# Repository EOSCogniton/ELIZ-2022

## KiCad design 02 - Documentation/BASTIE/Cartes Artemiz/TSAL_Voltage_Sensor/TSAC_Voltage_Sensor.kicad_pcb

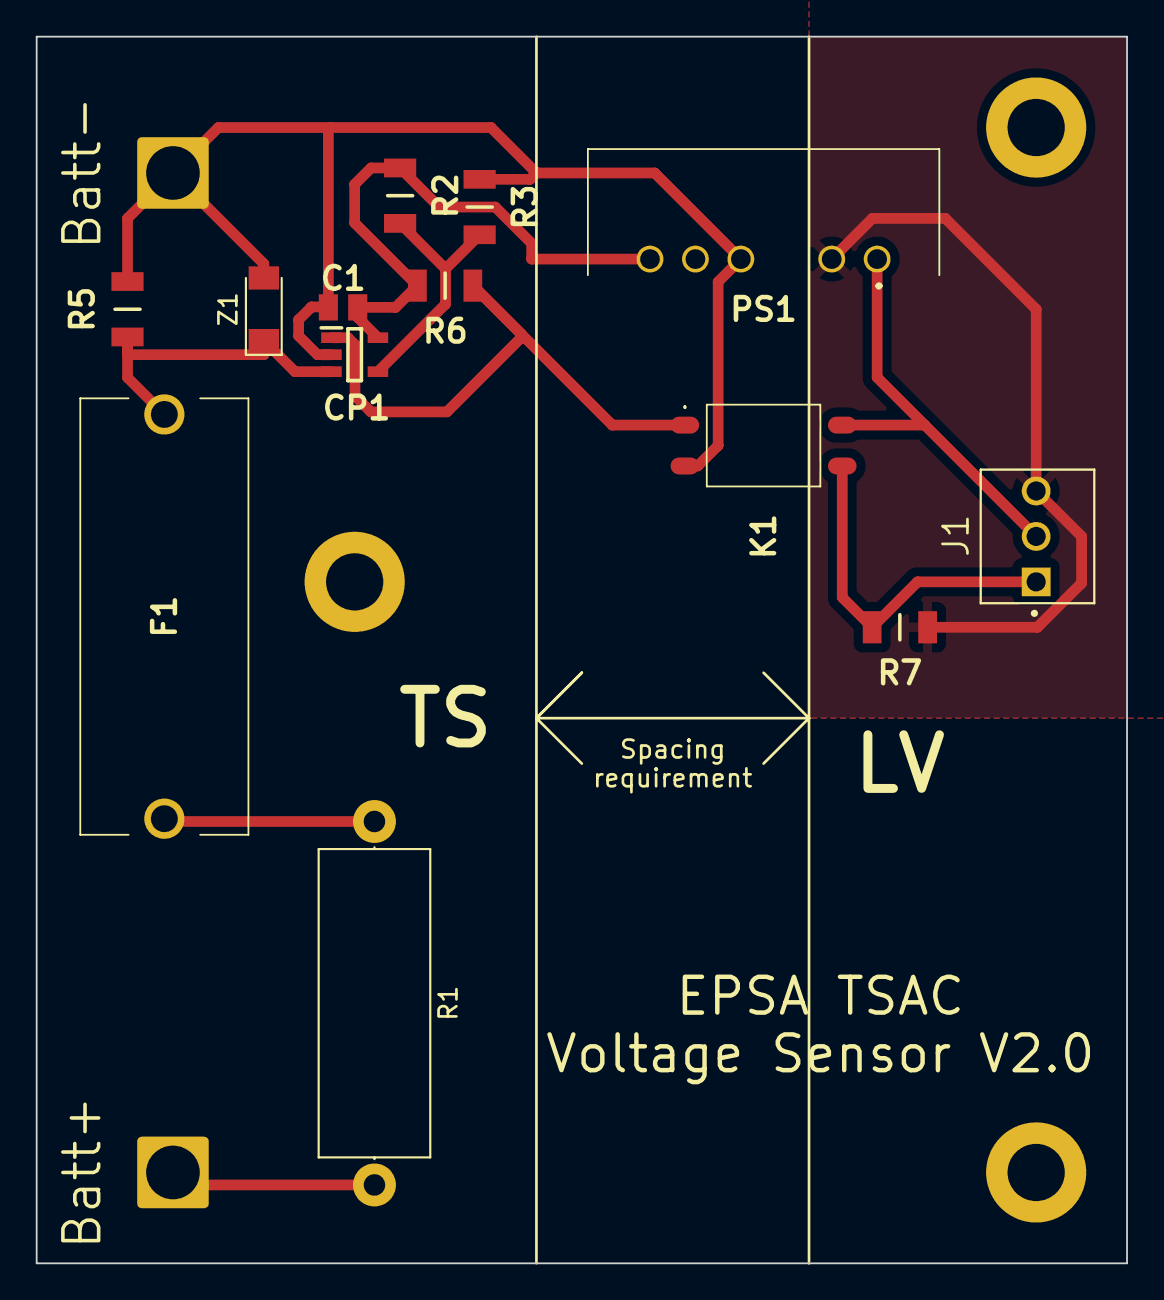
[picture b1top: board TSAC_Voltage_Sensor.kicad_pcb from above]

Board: 2 copper layers, 61.0 x 68.6 mm, 15 parts (0 on the bottom side), 10 nets.

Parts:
C1: Condensateur 0805Y1000104JXT; CAPC2012X130N
CP1: Comparateur TS391ILT; SOT95P280X145-5N
F1: Fuse; 0PTF0078P
J1: 3P Droit 22-11-2032; MOLEX_22-11-2032
K1: SSR CPC1394GR; CPC1394GR
PS1: Alim Iso PDM2-S5-S5-S; PDM2S5S5S
R1: Résistance RK73H2BLTDD2152F; R_Axial_DIN0617_L17.0mm_D6.0mm_P20.32mm_Horizontal
R2, R3, R5, R6, R7: Résistance RK73H2BLTDD2152F; RESC3216X70N
TP1, TP2: TestPoint; SolderWire-2.5sqmm_1x01_D2.4mm_OD3.6mm
Z1: Zener TZM5224B-GS08; D_MiniMELF

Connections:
0: C1.1, CP1.2 (VCC-), K1.2 (-_CONTROL), PS1.4 (0V), R3.2, R5.1, TP2.1, Z1.2
+5V: C1.2, CP1.5 (VCC+), PS1.6 (+VO), R2.2, R6.2
+5VA: J1.2, K1.4 (LOAD_2), PS1.1 (VIN)
+BATT: R1.2, TP1.1
Comp: CP1.1 (OUT), K1.1 (+_CONTROL), R6.1
Exit: J1.1, K1.3 (LOAD_1), R7.2
GND: J1.3, PS1.2 (GND), R7.1
unnamed: CP1.3 (IN-), F1.2, R5.2, Z1.1
unnamed: CP1.4 (IN+), R2.1, R3.1
unnamed: F1.1, R1.1

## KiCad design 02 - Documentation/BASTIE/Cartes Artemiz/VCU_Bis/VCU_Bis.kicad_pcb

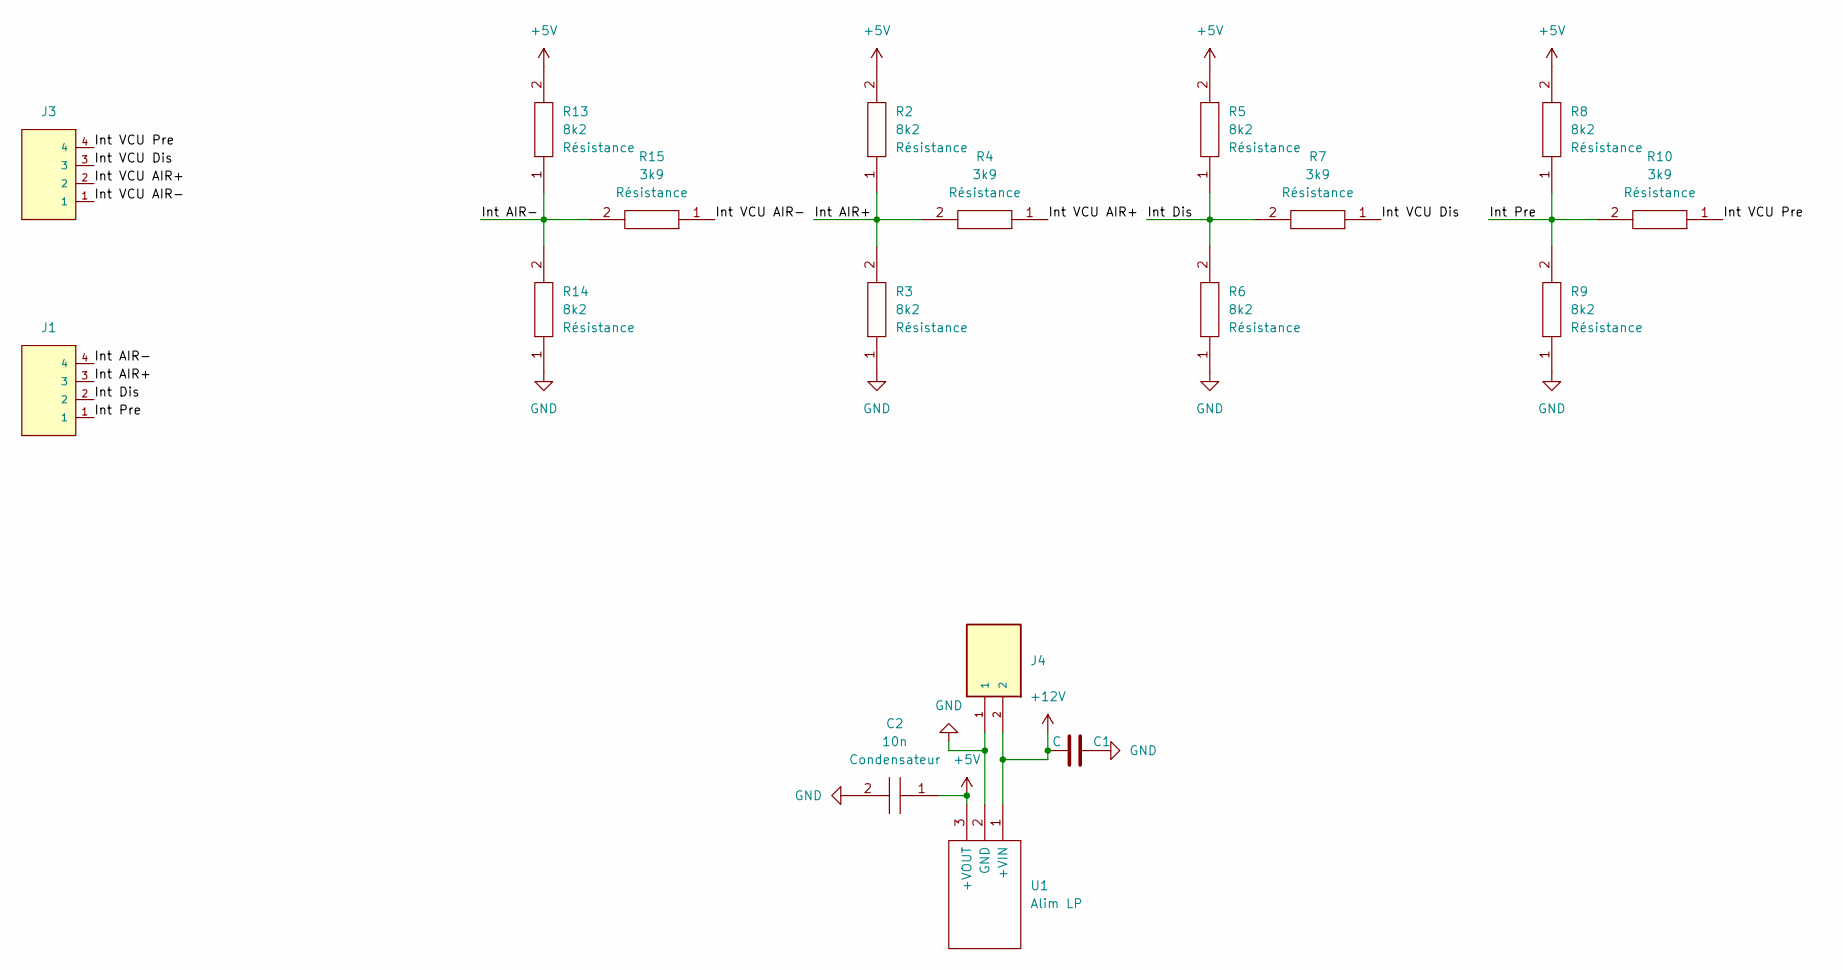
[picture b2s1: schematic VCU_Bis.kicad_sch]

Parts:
C1: C; CP_Radial_D5.0mm_P2.00mm
C2: 10n; CAPC2012X130N; Manufacturer_Part_Number 0805Y1000104JXT
J1, J3: 4P Droit 22-11-2042; MOLEX_22-11-2042; Manufacturer_Part_Number 22-11-2042; Mouser Part Number 538-22-11-2042
J4: 2P Droit 2-11-2022; MOLEX_22-11-2022; Manufacturer_Part_Number 22-11-2022; Mouser Part Number 538-22-11-2022
R2, R3, R5, R6, R8, R9, R13, R14: 8k2; RESC3216X70N; Manufacturer_Part_Number RK73H2BLTDD2152F; Mouser Part Number N/A
R4, R7, R10, R15: 3k9; RESC3216X70N; Manufacturer_Part_Number RK73H2BLTDD2152F; Mouser Part Number N/A
U1: Alim LP TSR_0.5-2450; TSR-0.5-2433; Manufacturer_Part_Number TSR 0.5-2450; Mouser Part Number 495-TSR0.5-2450

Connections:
+5V: C2.1, R2.2, R5.2, R8.2, R13.2, U1.3 (+VOUT)
+12V: C1.1, J4.2, U1.1 (+VIN)
/Int AIR+: J1.3, R2.1, R3.2, R4.2
/Int AIR-: J1.4, R13.1, R14.2, R15.2
/Int Dis: J1.2, R5.1, R6.2, R7.2
/Int Pre: J1.1, R8.1, R9.2, R10.2
/Int VCU AIR+: J3.2, R4.1
/Int VCU AIR-: J3.1, R15.1
/Int VCU Dis: J3.3, R7.1
/Int VCU Pre: J3.4, R10.1
GND: C1.2, C2.2, J4.1, R3.1, R6.1, R9.1, R14.1, U1.2 (GND)

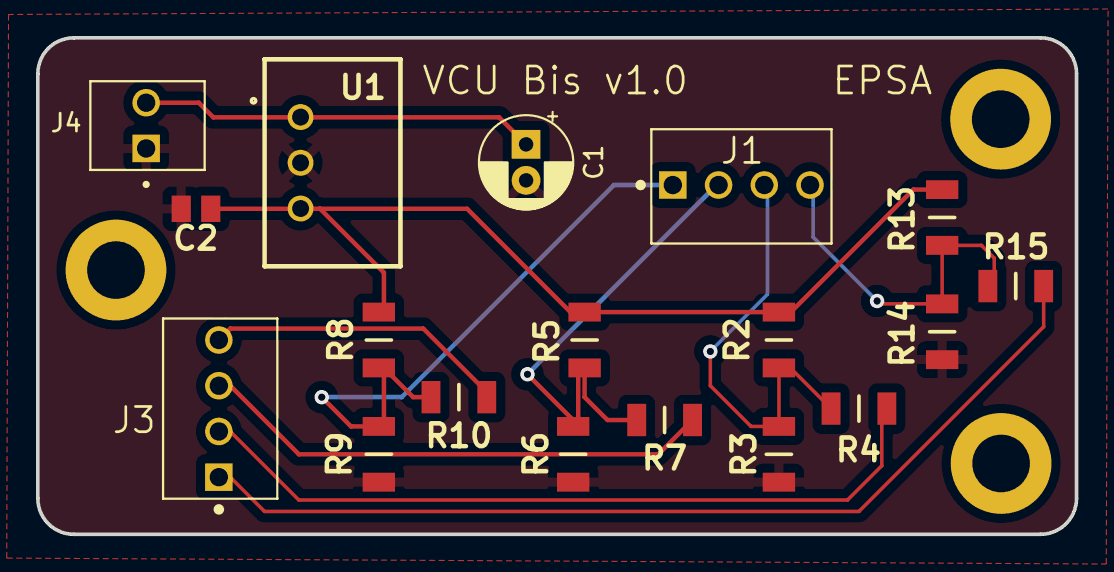
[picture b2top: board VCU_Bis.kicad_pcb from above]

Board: 2 copper layers, 57.7 x 27.6 mm, 18 parts (0 on the bottom side), 11 nets.

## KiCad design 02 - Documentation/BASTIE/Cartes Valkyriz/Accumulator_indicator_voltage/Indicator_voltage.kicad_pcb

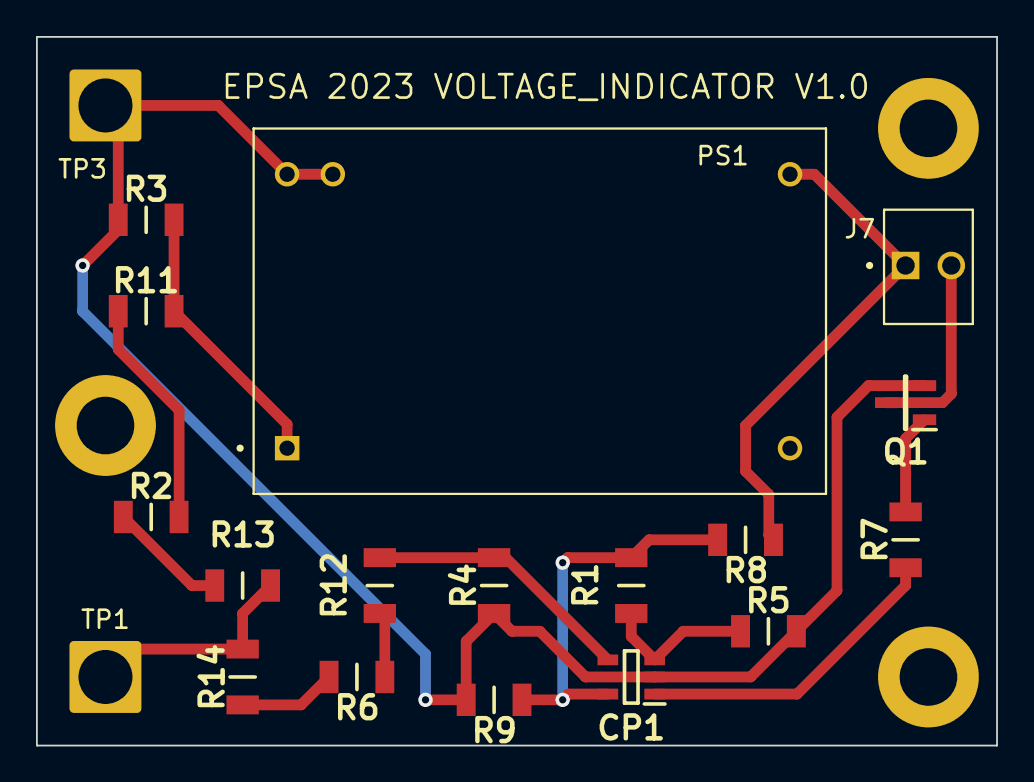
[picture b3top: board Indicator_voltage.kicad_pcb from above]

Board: 2 copper layers, 53.3 x 39.4 mm, 19 parts (0 on the bottom side), 14 nets.

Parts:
CP1: Comparateur TS391ILT; SOT95P280X145-5N
J7: 2P Droit 2-11-2022; MOLEX_22-11-2022
PS1: THR_3-7212WI; CONV_THR_3-7212WI
Q1: NMOS SQ2348ES-T1_GE3; SOT95P237X112-3N
R1: 18k; RESC3216X70N
R2, R3, R6, R11, R12, R13, R14: 390k; RESC3216X70N
R4: 10k; RESC3216X70N
R5: 2k; RESC3216X70N
R7, R9: 1k; RESC3216X70N
R8: 1k4; RESC3216X70N
TP1, TP3: type="R" model="TestPoint" lib=""; SolderWire-2.5sqmm_1x01_D2.4mm_OD3.6mm

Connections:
0: CP1.2 (VCC-), PS1.23 (-VIN(GND)), PS1.24 (-VIN(GND)), Q1.2, R3.1, R4.1, R5.2, R9.2, TP3.1
5V: CP1.5 (VCC+), R1.1, R8.2, R9.1
12V: J7.1, PS1.13 (+VOUT), R8.1
/150V: PS1.1 (+VIN(VCC)), R3.2, R11.2
HV+: R13.1, R14.2, TP1.1
LED-: J7.2, Q1.3
unnamed: CP1.4 (IN+), R4.2, R12.1
unnamed: CP1.3 (IN-), R1.2, R5.1
unnamed: CP1.1 (OUT), R7.1
unnamed: Q1.1, R7.2
unnamed: R2.2, R11.1
unnamed: R6.1, R12.2
unnamed: R2.1, R13.2
unnamed: R6.2, R14.1

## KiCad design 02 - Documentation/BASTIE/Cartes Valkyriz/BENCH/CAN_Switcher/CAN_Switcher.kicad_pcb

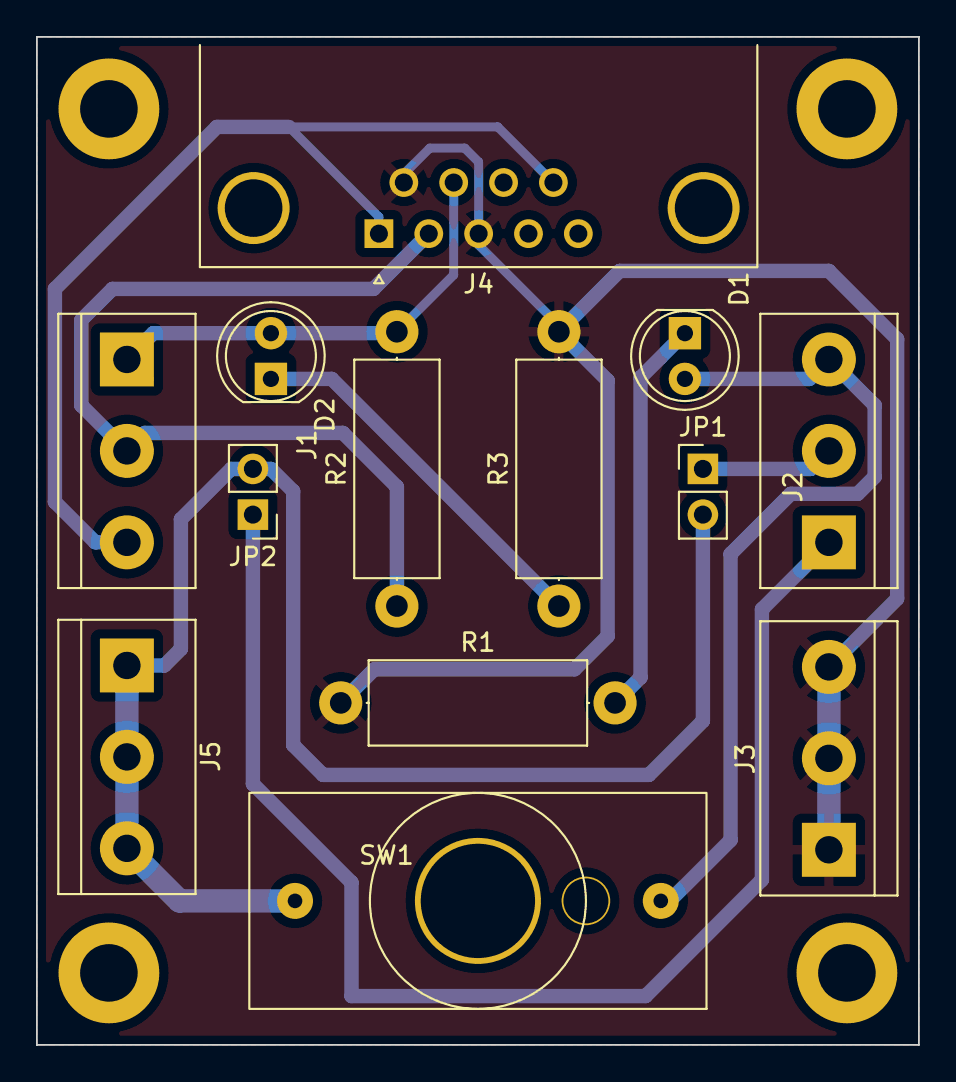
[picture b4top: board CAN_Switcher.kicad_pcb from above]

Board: 2 copper layers, 49.0 x 56.0 mm, 13 parts (0 on the bottom side), 10 nets.

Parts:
D1, D2: LED; LED_D5.0mm
J1, J2, J3, J5: Screw_Terminal_01x03; TerminalBlock_bornier-3_P5.08mm
J4: DB9_Female_MountingHoles; DSUB-9_Female_Horizontal_P2.77x2.84mm_EdgePinOffset7.70mm_H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
JP1, JP2: Jumper_2_Bridged; PinHeader_1x02_P2.54mm_Vertical
R1, R2, R3: R; R_Axial_DIN0414_L11.9mm_D4.5mm_P15.24mm_Horizontal
SW1: SW_MEC_5G; Interrupteur 1Channel

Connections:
+12V: J5.1, J5.2, J5.3, JP1.2 (B), JP2.2 (B), SW1.3 (B)
/AC Charging wake up: J2.2, JP1.1 (A)
/CAN_H_Peak: D2.2 (A), J1.1, J4.7, R2.2
/CAN_L_Peak: J1.2, J4.2, R2.1
/Can_V+: J1.3, J4.1, J4.9
/DC Charging Wake up Signal: J2.1, JP2.1 (A)
/KEYON: D1.2 (A), J2.3, SW1.2 (A)
GND: J3.1, J3.2, J3.3, J4.3, J4.6, R1.1, R3.2
unnamed: D1.1 (K), R1.2
unnamed: D2.1 (K), R3.1

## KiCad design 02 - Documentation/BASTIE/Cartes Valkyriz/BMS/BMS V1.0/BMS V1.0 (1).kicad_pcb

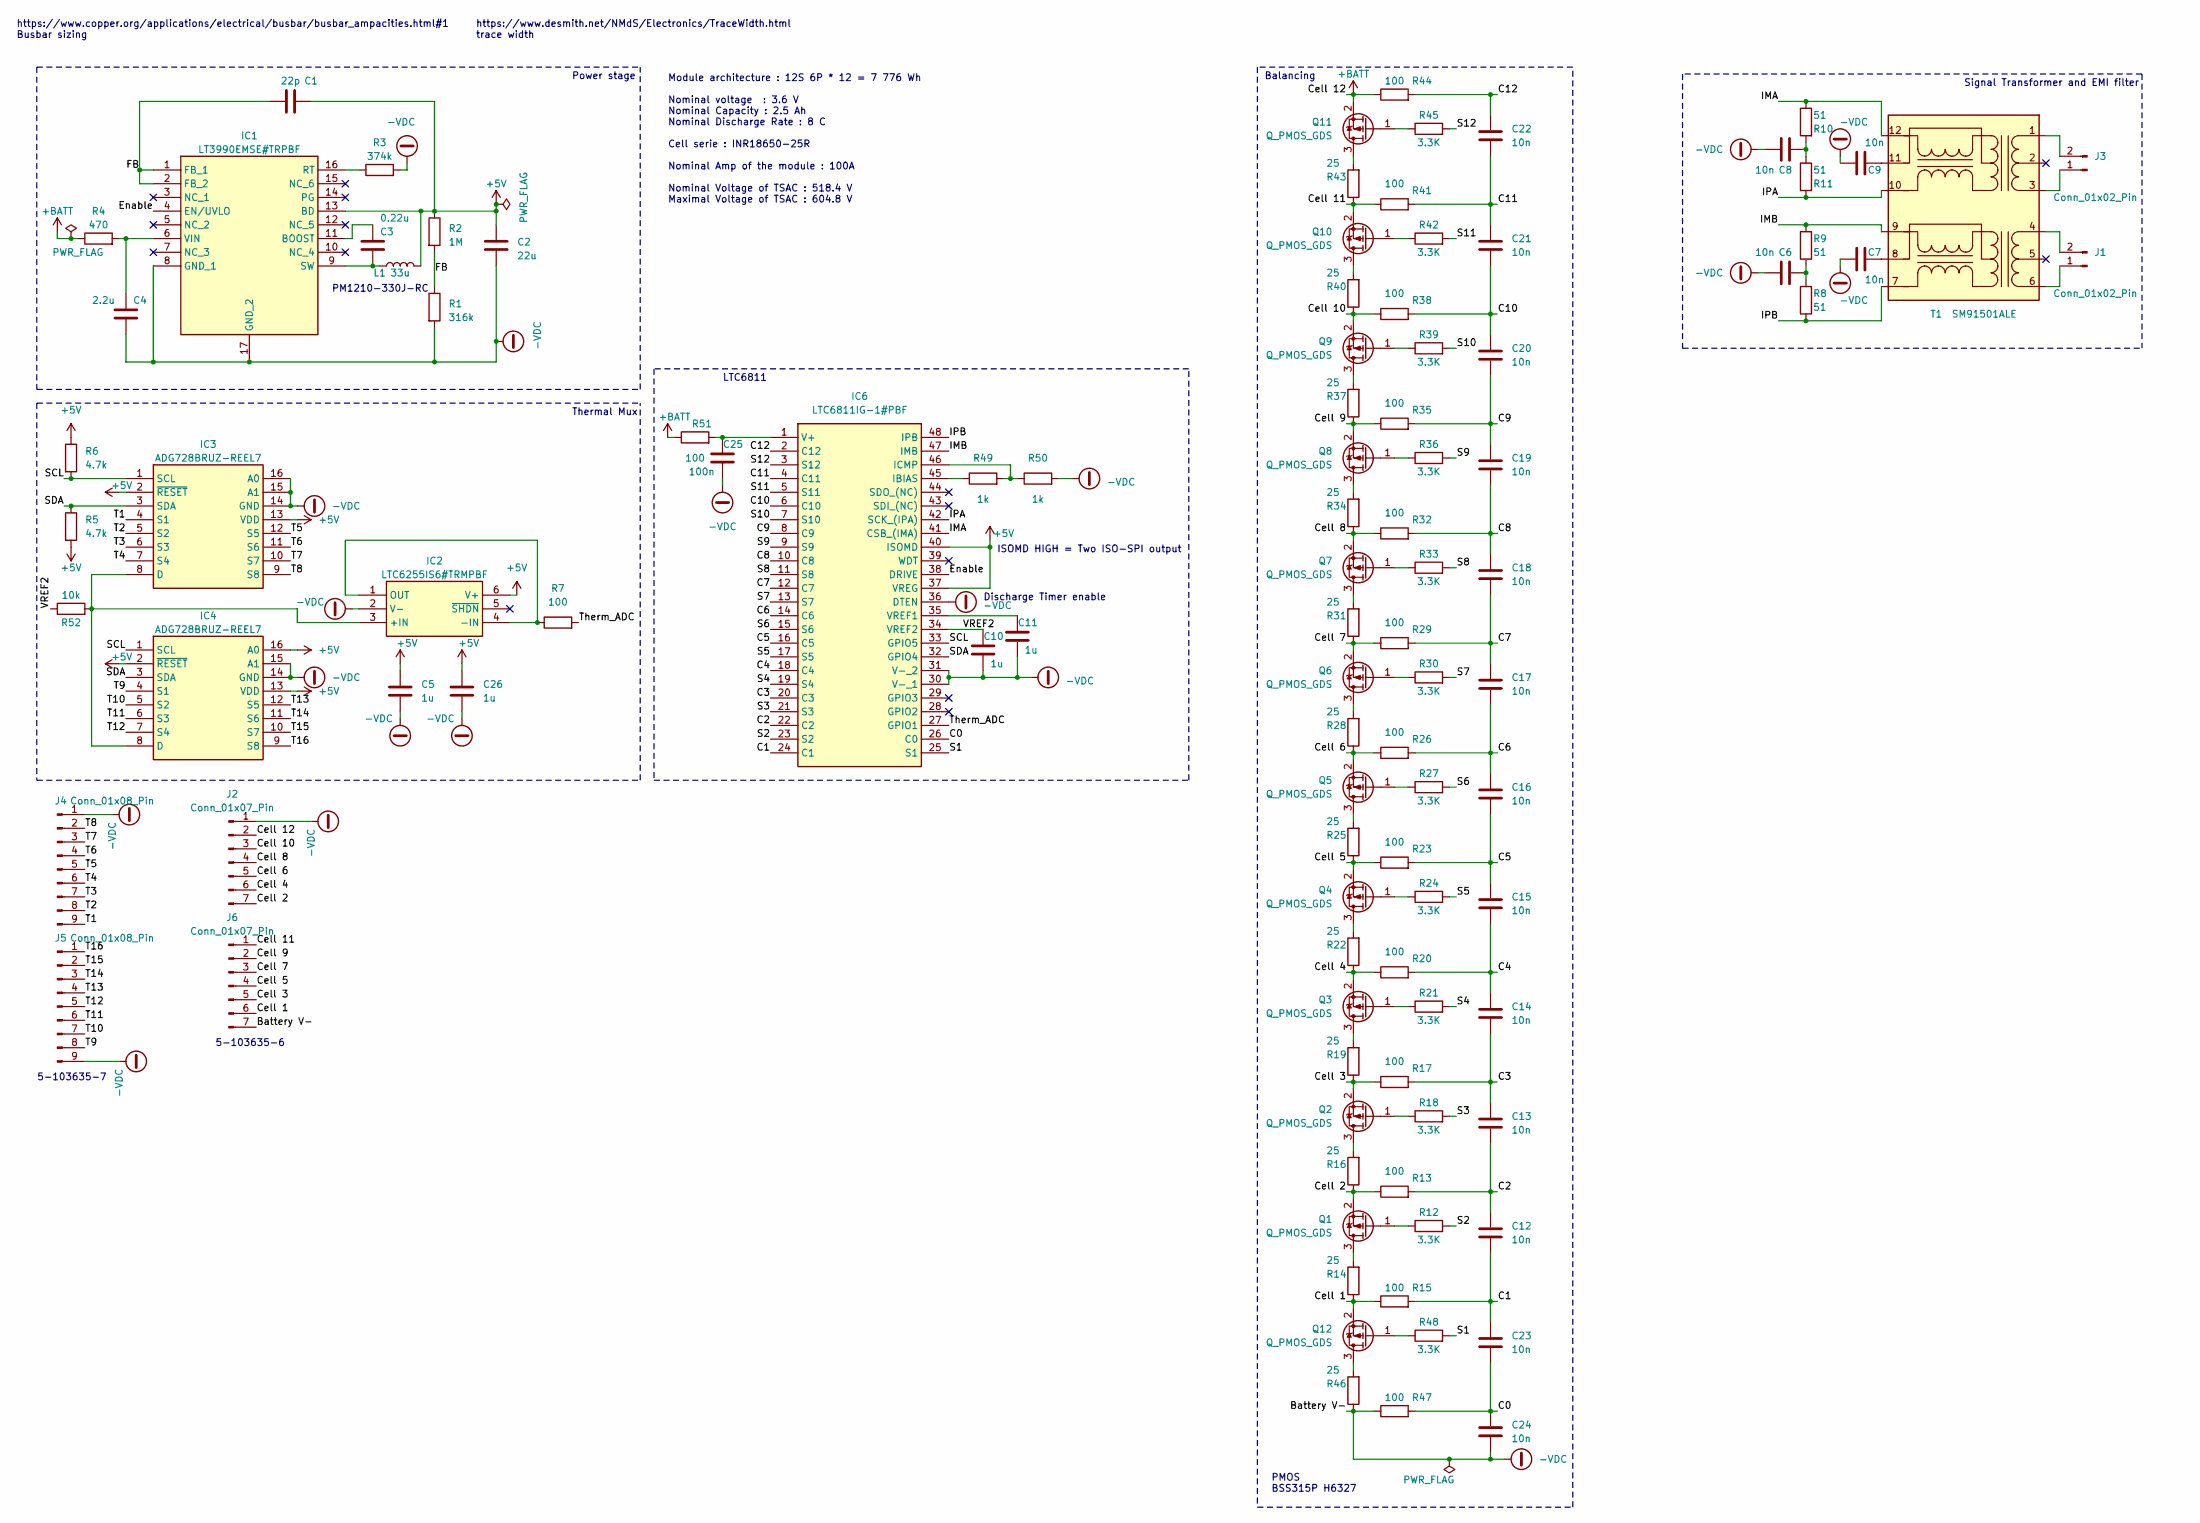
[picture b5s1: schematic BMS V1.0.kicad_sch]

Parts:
C1: 22p; C_0805_2012Metric_Pad1.18x1.45mm_HandSolder
C2: 22u; C_0805_2012Metric_Pad1.18x1.45mm_HandSolder
C3: 0.22u; C_0805_2012Metric_Pad1.18x1.45mm_HandSolder
C4: 2.2u; C_0805_2012Metric_Pad1.18x1.45mm_HandSolder
C5, C10, C11, C26: 1u; C_0805_2012Metric_Pad1.18x1.45mm_HandSolder
C6, C7, C8, C9, C12, C13, C14, C15, C16, C17, C18, C19, C20, C21, C22, C23, C24: 10n; C_0805_2012Metric_Pad1.18x1.45mm_HandSolder
C25: 100n; C_0805_2012Metric_Pad1.18x1.45mm_HandSolder
IC1: LT3990EMSE#TRPBF; SOP50P490X110-17N; Mouser Part Number 584-LT3990EMSE#TRPBF
IC2: LTC6255IS6#TRMPBF; SOT95P280X100-6N; Mouser Part Number 584-LTC6255IS6TRMPBF
IC3, IC4: ADG728BRUZ-REEL7; SOP65P640X120-16N; Mouser Part Number 584-ADG728BRUZ-R7
IC6: LTC6811IG-1#PBF; SOP50P780X200-48N; Mouser Part Number 584-LTC6811IG-1#PBF
J1, J3: Conn_01x02_Pin; RHDR2W97P0X254_1X2_654X508X1379P
J2, J6: Conn_01x07_Pin; SHDRRA7W77P0X254_1X7_2032X1359X699P
J4, J5: Conn_01x08_Pin; SHDRRA9W69P0X254_1X9_2527X1359X741P
L1: 33u; L_1210_3225Metric_Pad1.42x2.65mm_HandSolder
Q1, Q2, Q3, Q4, Q5, Q6, Q7, Q8, Q9, Q10, Q11, Q12: Q_PMOS_GDS; SOT-23-3
R1: 316k; R_1206_3216Metric_Pad1.30x1.75mm_HandSolder
R2: 1M; R_1206_3216Metric_Pad1.30x1.75mm_HandSolder
R3: 374k; R_1206_3216Metric_Pad1.30x1.75mm_HandSolder
R4: 470; R_1206_3216Metric_Pad1.30x1.75mm_HandSolder
R5, R6: 4.7k; R_1206_3216Metric_Pad1.30x1.75mm_HandSolder
R7, R13, R15, R17, R20, R23, R26, R29, R32, R35, R38, R41, R44, R47, R51: 100; R_1206_3216Metric_Pad1.30x1.75mm_HandSolder
R8, R9, R10, R11: 51; R_1206_3216Metric_Pad1.30x1.75mm_HandSolder
R12, R18, R21, R24, R27, R30, R33, R36, R39, R42, R45, R48: 3.3K; R_1206_3216Metric_Pad1.30x1.75mm_HandSolder
R14, R16, R19, R22, R25, R28, R31, R34, R37, R40, R43, R46: 25; R_2512_6332Metric_Pad1.40x3.35mm_HandSolder
R49, R50: 1k; R_1206_3216Metric_Pad1.30x1.75mm_HandSolder
R52: 10k; R_1206_3216Metric_Pad1.30x1.75mm_HandSolder
T1: SM91501ALE; SOP200P1473X500-12N; Mouser Part Number 652-SM91501ALE

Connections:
+5V: C1.2, C2.2, C5.1, C26.1, IC1.13 (BD), IC2.6 (V+), IC3.2 (~RESET), IC3.13 (VDD), IC4.2 (~RESET), IC4.13 (VDD), IC4.16 (A0), IC6.37 (VREG), IC6.40 (ISOMD), L1.2, R2.1, R5.2, R6.1
+BATT: J2.2, Q11.2 (S), R4.1, R44.1, R51.1
-VDC: C2.1, C4.1, C5.2, C6.1, C7.1, C8.1, C9.1, C10.2, C11.2, C24.2, C25.2, C26.2, IC1.8 (GND_1), IC1.17 (GND_2), IC2.2 (V-), IC3.14 (GND), IC3.15 (A1), IC3.16 (A0), IC4.14 (GND), IC4.15 (A1), IC6.30 (V-_1), IC6.31 (V-_2), IC6.36 (DTEN), J2.1, J4.1, J5.9, J6.7, R1.2, R3.2, R46.1, R47.1, R50.2
/C0: C23.2, C24.1, IC6.26 (C0), R47.2
/C1: C12.2, C23.1, IC6.24 (C1), R15.2
/C2: C12.1, C13.2, IC6.22 (C2), R13.2
/C3: C13.1, C14.2, IC6.20 (C3), R17.2
/C4: C14.1, C15.2, IC6.18 (C4), R20.2
/C5: C15.1, C16.2, IC6.16 (C5), R23.2
/C6: C16.1, C17.2, IC6.14 (C6), R26.2
/C7: C17.1, C18.2, IC6.12 (C7), R29.2
/C8: C18.1, C19.2, IC6.10 (C8), R32.2
/C9: C19.1, C20.2, IC6.8 (C9), R35.2
/C10: C20.1, C21.2, IC6.6 (C10), R38.2
/C11: C21.1, C22.2, IC6.4 (C11), R41.2
/C12: C22.1, IC6.2 (C12), R44.2
/Cell 1: J6.6, Q12.2 (S), R14.1, R15.1
/Cell 2: J2.7, Q1.2 (S), R13.1, R16.1
/Cell 3: J6.5, Q2.2 (S), R17.1, R19.1
/Cell 4: J2.6, Q3.2 (S), R20.1, R22.1
/Cell 5: J6.4, Q4.2 (S), R23.1, R25.1
/Cell 6: J2.5, Q5.2 (S), R26.1, R28.1
/Cell 7: J6.3, Q6.2 (S), R29.1, R31.1
/Cell 8: J2.4, Q7.2 (S), R32.1, R34.1
/Cell 9: J6.2, Q8.2 (S), R35.1, R37.1
/Cell 10: J2.3, Q9.2 (S), R38.1, R40.1
/Cell 11: J6.1, Q10.2 (S), R41.1, R43.1
/Enable: IC1.4 (EN/UVLO), IC6.38 (DRIVE)
/FB: C1.1, IC1.1 (FB_1), IC1.2 (FB_2), R1.1, R2.2
/IMA: IC6.41 (CSB_(IMA)), R10.1, T1.12 (SEC1_3)
/IMB: IC6.47 (IMB), R9.2, T1.9 (SEC2_3)
/IPA: IC6.42 (SCK_(IPA)), R11.2, T1.10 (SEC1_1)
/IPB: IC6.48 (IPB), R8.1, T1.7 (SEC2_1)
/S1: IC6.25 (S1), R48.2
/S2: IC6.23 (S2), R12.2
/S3: IC6.21 (S3), R18.2
/S4: IC6.19 (S4), R21.2
/S5: IC6.17 (S5), R24.2
/S6: IC6.15 (S6), R27.2
/S7: IC6.13 (S7), R30.2
/S8: IC6.11 (S8), R33.2
/S9: IC6.9 (S9), R36.2
/S10: IC6.7 (S10), R39.2
/S11: IC6.5 (S11), R42.2
/S12: IC6.3 (S12), R45.2
/SCL: IC3.1 (SCL), IC4.1 (SCL), IC6.33 (GPIO5), R6.2
/SDA: IC3.3 (SDA), IC4.3 (SDA), IC6.32 (GPIO4), R5.1
/T1: IC3.4 (S1), J4.9
/T2: IC3.5 (S2), J4.8
/T3: IC3.6 (S3), J4.7
/T4: IC3.7 (S4), J4.6
/T5: IC3.12 (S5), J4.5
/T6: IC3.11 (S6), J4.4
/T7: IC3.10 (S7), J4.3
/T8: IC3.9 (S8), J4.2
/T9: IC4.4 (S1), J5.8
/T10: IC4.5 (S2), J5.7
/T11: IC4.6 (S3), J5.6
/T12: IC4.7 (S4), J5.5
/T13: IC4.12 (S5), J5.4
/T14: IC4.11 (S6), J5.3
/T15: IC4.10 (S7), J5.2
/T16: IC4.9 (S8), J5.1
/Therm_ADC: IC6.27 (GPIO1), R7.2
/VREF2: C10.1, IC6.34 (VREF2), R52.1
unnamed: C6.2, R8.2, R9.1
unnamed: C8.2, R10.2, R11.1
unnamed: C3.2, IC1.11 (BOOST)
unnamed: IC1.16 (RT), R3.1
unnamed: C3.1, IC1.9 (SW), L1.1
unnamed: C4.2, IC1.6 (VIN), R4.2
unnamed: IC2.3 (+IN), IC3.8 (D), IC4.8 (D), R52.2
unnamed: IC2.1 (OUT), IC2.4 (-IN), R7.1
unnamed: IC6.45 (IBIAS), R49.1
unnamed: IC6.46 (ICMP), R49.2, R50.1
unnamed: C25.1, IC6.1 (V+), R51.2
unnamed: C11.1, IC6.35 (VREF1)
unnamed: J1.1, T1.6 (PRI2_3)
unnamed: J1.2, T1.4 (PRI2_1)
unnamed: J3.1, T1.3 (PRI1_3)
unnamed: J3.2, T1.1 (PRI1_1)
unnamed: Q1.3 (D), R14.2
unnamed: Q1.1 (G), R12.1
unnamed: Q2.3 (D), R16.2
unnamed: Q2.1 (G), R18.1
unnamed: Q3.3 (D), R19.2
unnamed: Q3.1 (G), R21.1
unnamed: Q4.3 (D), R22.2
unnamed: Q4.1 (G), R24.1
unnamed: Q5.3 (D), R25.2
unnamed: Q5.1 (G), R27.1
unnamed: Q6.3 (D), R28.2
unnamed: Q6.1 (G), R30.1
unnamed: Q7.3 (D), R31.2
unnamed: Q7.1 (G), R33.1
unnamed: Q8.3 (D), R34.2
unnamed: Q8.1 (G), R36.1
unnamed: Q9.3 (D), R37.2
unnamed: Q9.1 (G), R39.1
unnamed: Q10.3 (D), R40.2
unnamed: Q10.1 (G), R42.1
unnamed: Q11.3 (D), R43.2
unnamed: Q11.1 (G), R45.1
unnamed: Q12.3 (D), R46.2
unnamed: Q12.1 (G), R48.1
unnamed: C9.2, T1.11 (SEC1_2)
unnamed: C7.2, T1.8 (SEC2_2)

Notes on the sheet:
Module architecture : 12S 6P * 12 = 7 776 Wh Nominal voltage : 3.6 V Nominal Capacity : 2.5 Ah Nominal Discharge Rate : 8 C Cell serie : INR18650-25R Nominal Amp of the module : 100A Nominal Voltage of TSAC : 518.4 V Maximal Voltage of TSAC : 604.8 V
PMOS BSS315P H6327
PM1210-330J-RC
Balancing
Thermal Mux
Power stage
Signal Transformer and EMI filter
LTC6811
https://www.desmith.net/NMdS/Electronics/TraceWidth.html trace width
5-103635-7
https://www.copper.org/applications/electrical/busbar/busbar_ampacities.html#1 Busbar sizing
5-103635-6
ISOMD HIGH = Two ISO-SPI output
Discharge Timer enable

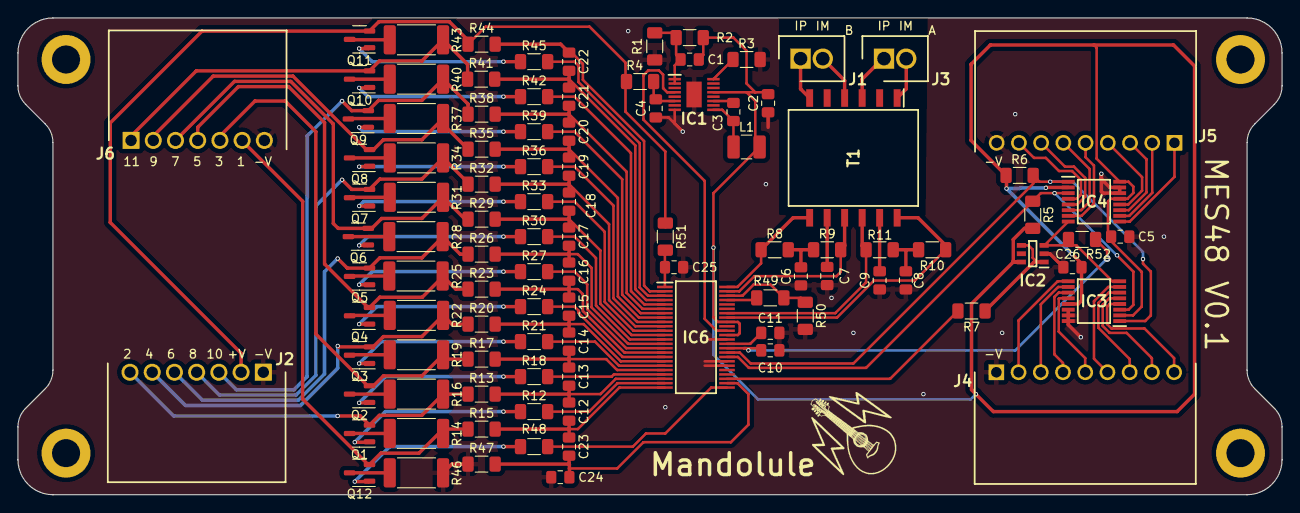
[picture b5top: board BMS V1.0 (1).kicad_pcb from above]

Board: 2 copper layers, 144.5 x 54.5 mm, 104 parts (0 on the bottom side), 107 nets.

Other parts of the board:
Ref**: Val**; Mandolule Silk

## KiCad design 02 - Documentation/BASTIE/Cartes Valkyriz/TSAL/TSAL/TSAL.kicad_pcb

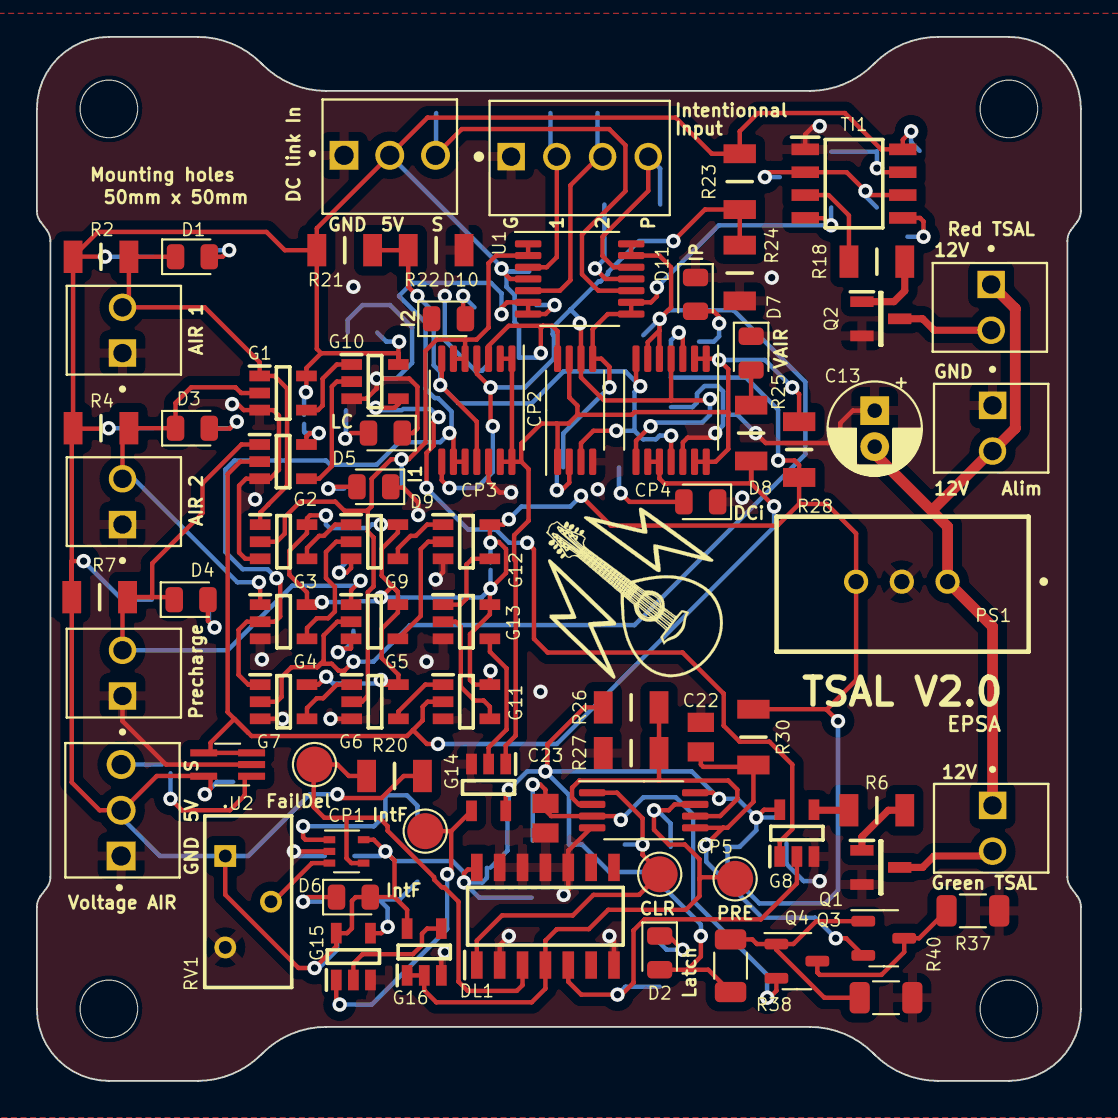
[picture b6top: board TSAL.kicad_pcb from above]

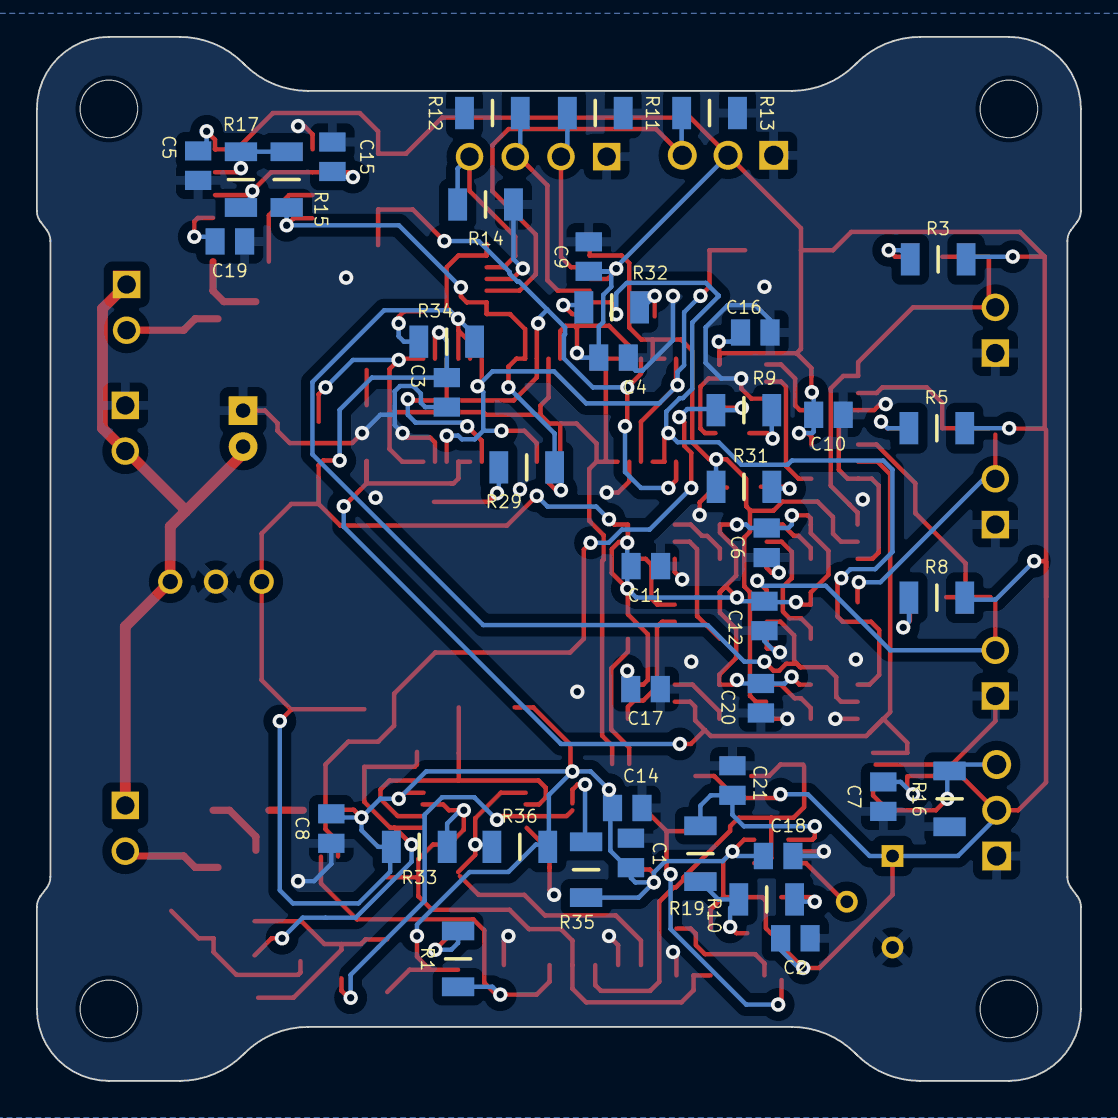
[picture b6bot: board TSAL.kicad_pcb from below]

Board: 2 copper layers, 58.0 x 58.0 mm, 122 parts (41 on the bottom side), 65 nets.

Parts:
C1, C2, C3, C4, C5, C6, C7, C8, C9, C10, C11, C12, C14, C16, C17, C18, C20: 10u; CAPC2012X130N
C13: C; CP_Radial_D5.0mm_P2.00mm
C15, C23: 1u; CAPC2012X130N
C19: 0.01u; CAPC2012X130N
C21, C22: 2.2u; CAPC2012X130N
CP1: Comparator; SOT-353_SC-70-5
CP2, CP5: Comparator_Dual; TSSOP-8_4.4x3mm_P0.65mm
CP3, CP4: Comparator_Quad; TSSOP-14_4.4x5mm_P0.65mm
D1, D2, D3, D4, D5, D6, D7, D8, D9, D10, D11: LED; LED_0805_2012Metric
DL1: Bascule D SN74HCS72QDRQ1; SOIC127P600X175-14N
G1, G2, G3, G4, G5, G6, G8, G10, G11, G14: Gate AND SN74AHCT1G08DBVR; SOT95P280X145-5N
G7, G9, G12, G15: Gate OR SN74AHCT1G32DBVR; SOT95P280X145-5N
G13, G16: Gate NOR SN74AHCT1G02DBVR; SOT95P280X145-5N
H1, H2, H3, H4: MountingHole; MountingHole_3.2mm_M3
J1, J2, J3, J5, J6, J9: 2P Droit 2-11-2022; MOLEX_22-11-2022
J4, J8: 3P Droit 22-11-2032; MOLEX_22-11-2032
J7: 4P Droit 22-11-2042; MOLEX_22-11-2042
PS1: Alim HP TSR_2-2450; TSR-2
Q1, Q2: NMOS SQ2348ES-T1_GE3; SOT95P237X112-3N
Q3, Q4: PMOS SI2343CDS-T1-GE3; SOT-23-3
R1, R3, R5, R8, R9, R10, R25, R29, R31, R32, R34: 500; RESC3216X70N
R2, R4, R6, R7, R18, R20, R28: 10k; RESC3216X70N
R11, R12, R13, R14, R16, R30, R35: 500k; RESC3216X70N
R15: 2k; RESC3216X70N
R17: 200k; RESC3216X70N
R19: 390k; RESC3216X70N
R21, R24: 12k; RESC3216X70N
R22, R23: 82k; RESC3216X70N
R26: 100k; RESC3216X70N
R27: 50k; RESC3216X70N
R33, R36: 5k; RESC3216X70N
R37: 1k; R_1206_3216Metric
R38: 10k; R_1206_3216Metric
R40: 100k; R_1206_3216Metric
RV1: Varystor 3296Y-1-223LF; 3296Y1223LF
Ref**: Val**; Mandolule Silk
TI1: Timer 555 LM555CMX_NOPB; SOIC127P600X175-8N
TP1, TP2, TP3, TP4: type="R" model="TestPoint" lib=""; TestPoint_Pad_D2.0mm
U1: Opamp_Quad; TSSOP-14_4.4x5mm_P0.65mm
U2: Opamp; SOT-353_SC-70-5_Handsoldering

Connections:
+5V: C1.2, C2.2, C3.2, C4.2, C5.2, C6.2, C7.2, C8.2, C9.2, C10.2, C11.2, C12.2, C14.2, C16.2, C17.2, C18.2, C20.2, CP1.5 (V+), CP2.8 (V+), CP3.3 (V+), CP4.3 (V+), CP5.8 (V+), D2.2 (A), D6.2 (A), DL1.14 (VCC), G1.5 (VCC), G2.5 (VCC), G3.5 (VCC), G4.5 (VCC), G5.5 (VCC), G6.5 (VCC), G7.5 (VCC), G8.5 (VCC), G9.5 (VCC), G10.5 (VCC), G11.5 (VCC), G12.5 (VCC), G13.5 (VCC), G14.5 (VCC), G15.5 (VCC), G16.5 (VCC), J4.2, J8.2, PS1.3 (+VOUT), R2.2, R3.2, R4.2, R5.2, R7.2, R8.2, R20.2, R21.2, R23.2, R26.2, R28.1, R30.2, R33.2, R35.2, R36.2, R38.1, RV1.1 (CCW), TI1.8 (+VCC), U1.4 (V+), U2.5 (V+)
+12V: C13.2, J5.1, J6.2, J9.1, PS1.1 (+VIN)
/0.75V: CP2.6 (-), CP3.4 (-), CP3.8 (-), CP4.4 (-), CP4.8 (-), R23.1, R24.2
/4.25V: CP2.3 (+), CP3.7 (+), CP3.11 (+), CP4.7 (+), CP4.11 (+), R21.1, R22.2
/AIR_1: D1.1 (K), G1.1, G3.1, J1.2, R2.1
/AIR_2: D3.1 (K), G1.2, G4.1, J2.2, R4.1
/CLR: CP5.1, DL1.1 (1~CLR), R36.1, TP4.1
/Clign: R18.1, TI1.3 (OUTPUT)
/DC-Link_In: CP2.2 (-), CP2.5 (+), R15.2, R29.2, TI1.4 (RESET), U1.8, U1.9 (-)
/INT: DL1.5 (1Q), G8.2, R1.1
/Int_AIR_1: CP3.5 (+), CP3.6 (-), G3.2, G6.2, R31.2, U1.1, U1.2 (-)
/Int_AIR_2: CP3.9 (+), CP3.10 (-), G4.2, G7.1, R32.2, U1.6 (-), U1.7
/Int_PreCharge: CP4.5 (+), CP4.6 (-), G5.2, G7.2, R34.2, U1.13 (-), U1.14
/Int_del: CP1.4, DL1.3 (1~CLK), R20.1, TP2.1
/Int_log: G14.4, G15.1, TP1.1
/Lightning_cond: G8.1, G10.4, R9.1
/PRE: CP5.7, DL1.4 (1~PRE), G16.1, G16.2, R33.1, TP3.1
/PreCharge: D4.1 (K), G2.1, G5.1, J3.2, R7.1
/Raw_DC-Link_In: J8.3, R13.2, U1.10 (+)
/Raw_Int_AIR_1: J7.2, R11.2, U1.3 (+)
/Raw_Int_AIR_2: J7.3, R12.2, U1.5 (+)
/Raw_Int_PreCharge: J7.4, R14.2, U1.12 (+)
/Raw_VoltageAIR: J4.3, R16.2, U2.1 (+)
/SCS compliance: CP2.1, CP2.7, CP3.1, CP3.2, CP3.13, CP3.14, CP4.1, CP4.2, CP4.13, CP4.14, G14.1, R28.2
/VoltageAIR: CP4.9 (+), CP4.10 (-), G2.2, G11.2, R25.2, U2.3 (-), U2.4
/dis1: C22.2, CP5.5 (+), Q3.2, R30.1
/dis2: C23.2, CP5.3 (+), Q4.2, R35.1
/mid_Pot: CP5.2 (-), CP5.6 (-), R26.1, R27.2
GND: C1.1, C2.1, C3.1, C4.1, C5.1, C6.1, C7.1, C8.1, C9.1, C10.1, C11.1, C12.1, C13.1, C14.1, C15.1, C16.1, C17.1, C18.1, C19.1, C20.1, C21.2, C22.1, C23.1, CP1.2 (V-), CP2.4 (V-), CP3.12 (V-), CP4.12 (V-), CP5.4 (V-), D5.1 (K), D7.1 (K), D8.1 (K), D9.1 (K), D10.1 (K), D11.1 (K), DL1.2 (1D), DL1.7 (GND), DL1.10 (2~PRE), DL1.11 (2~CLK), DL1.12 (2D), DL1.13 (2~CLR), G1.3 (GND), G2.3 (GND), G3.3 (GND), G4.3 (GND), G5.3 (GND), G6.3 (GND), G7.3 (GND), G8.3 (GND), G9.3 (GND), G10.3 (GND), G11.3 (GND), G12.3 (GND), G13.3 (GND), G14.3 (GND), G15.3 (GND), G16.3 (GND), J1.1, J2.1, J3.1, J4.1, J6.1, J7.1, J8.1, PS1.2 (GND), Q1.2, Q2.2, R11.1, R12.1, R13.1, R14.1, R16.1, R22.1, R24.1, R27.1, R37.1, R40.2, RV1.3 (CW), TI1.1 (GND), U1.11 (V-), U2.2 (V-)
unnamed: C21.1, CP1.1 (+), R19.2
unnamed: CP1.3 (-), RV1.2 (WIPER)
unnamed: D1.2 (A), R3.1
unnamed: D2.1 (K), R1.2
unnamed: D3.2 (A), R5.1
unnamed: D4.2 (A), R8.1
unnamed: D5.2 (A), R9.2
unnamed: D6.1 (K), R10.2
unnamed: D7.2 (A), R25.1
unnamed: D8.2 (A), R29.1
unnamed: D9.2 (A), R31.1
unnamed: D10.2 (A), R32.1
unnamed: D11.2 (A), R34.1
unnamed: G1.4, G10.1
unnamed: G3.4, G9.1
unnamed: G4.4, G9.2
unnamed: G6.1, G7.4
unnamed: G8.4, R6.1
unnamed: G2.4, G10.2
unnamed: G6.4, G11.1
unnamed: G11.4, G13.2
unnamed: G9.4, G12.1
unnamed: G5.4, G12.2
unnamed: G12.4, G13.1
unnamed: G13.4, G14.2
unnamed: G15.2, G16.4
unnamed: G15.4, R10.1, R19.1
unnamed: J5.2, Q1.3
unnamed: J9.2, Q2.3
unnamed: Q1.1, R6.2
unnamed: Q2.1, R18.2
unnamed: Q3.1, Q4.1, R38.2, R40.1
unnamed: Q3.3, Q4.3, R37.2
unnamed: C19.2, TI1.5 (CONTROL_VOLTAGE)
unnamed: R15.1, R17.2, TI1.7 (DISCHARGE)
unnamed: C15.2, R17.1, TI1.2 (TRIGGER), TI1.6 (THRESHOLD)
